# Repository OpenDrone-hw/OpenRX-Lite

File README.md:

# OpenRX Lite

Open-source 2.4 GHz ExpressLRS radio control receiver module with telemetry,
for any radio-controlled build: cars, boats, robots and aircraft. OpenRX Lite
combines an ESP32-C3 and SX1281 with an on-board ceramic link antenna in a
10.0 x 11.5 mm board.
It passes the received channels over serial (CRSF) on its RX and TX pads to a
controller, for example a flight controller or a vehicle or robot controller.

## Specifications

| | |
|---|---|
| Band | 2.4 GHz |
| Radio | SX1281 |
| Antenna | On-board ceramic |
| Telemetry power | 13 dBm (20 mW) |
| Protocol | CRSF |
| MCU | ESP32-C3 |
| Input | 5 V pad |
| Firmware | ExpressLRS |
| Flashing | Betaflight passthrough or Wi-Fi |
| Dimensions | 10.0 x 11.5 mm |
| PCB | 6-layer, 1.0 mm |

Technical write-up, part list and layout constraints: [AGENTS.md](AGENTS.md).

## In the line

What pairs with what, and what is available:
[opendrone.be](https://opendrone.be).

## Contributing

To load the KiCad-Library, use `git submodule update --init` or `git clone --recurse-submodules https://github.com/OpenDrone-hw/OpenRX-Lite`

Furthermore, see [CONTRIBUTING.md](CONTRIBUTING.md).

## License

Hardware licensed under [CERN-OHL-S-2.0](https://ohwr.org/cern_ohl_s_v2.txt),
see [LICENSE](LICENSE).

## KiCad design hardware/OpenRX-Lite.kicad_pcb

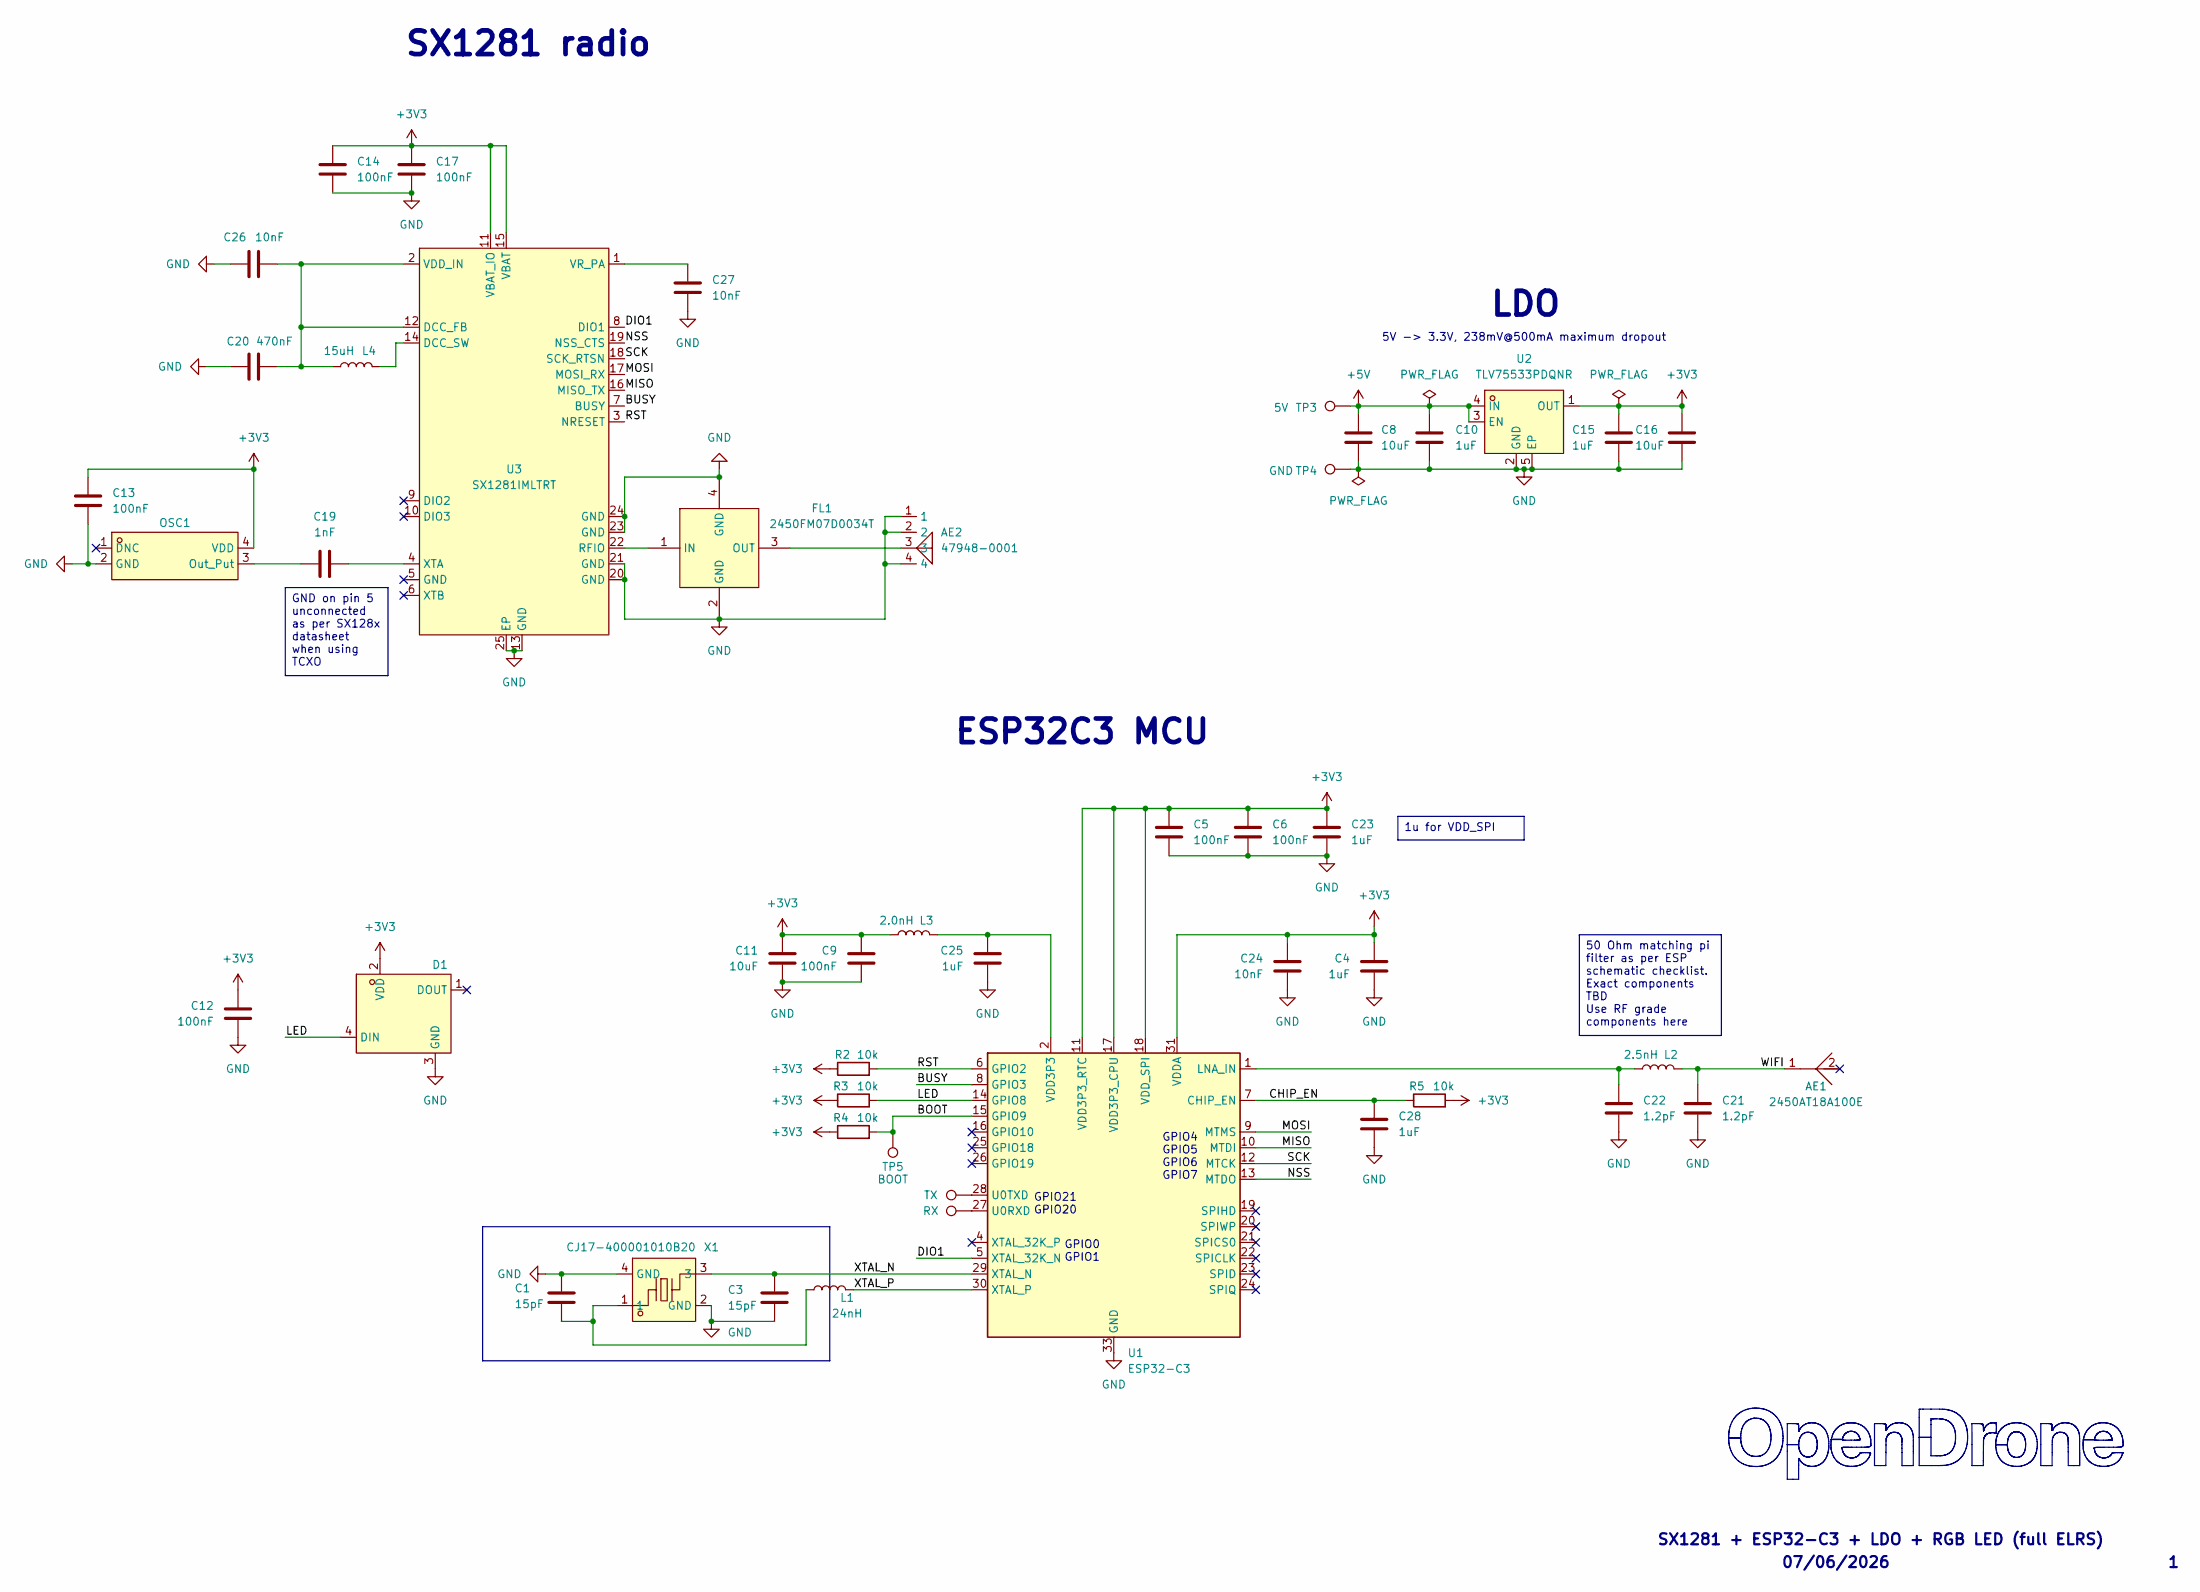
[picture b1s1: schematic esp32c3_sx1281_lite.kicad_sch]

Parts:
AE1: 2450AT18A100E; ANT-SMD_L3.2-W1.6; MPN 2450AT18A100E; LCSC Part C89334
AE2: 47948-0001; ANT-SMD_47948-0001; MPN 479480001; LCSC C152351
C1, C3: 15pF; C_0201_0603Metric; MPN GRM0335C1H150JA01D; LCSC C85891
C4, C10, C15, C23, C25, C28: 1uF; C_0201_0603Metric; MPN GRM033R61A105ME44D; LCSC C76935
C5, C6, C9, C12, C13, C14, C17: 100nF; C_0201_0603Metric; MPN GRM033R61E104KE14D; LCSC C76939
C8, C16: 10uF; C_0402_1005Metric; MPN CL05A106MQ5NUNC; LCSC C15525
C11: 10uF; C_0402_1005Metric; MPN GRM155R60J106ME44D; LCSC C76991
C19: 1nF; C_0201_0603Metric; MPN 0201B102K500NT; LCSC C66942
C20: 470nF; C_0201_0603Metric; MPN GRM033R60J474KE90D; LCSC C85926
C21, C22: 1.2pF; C_0201_0603Metric; MPN GRM0335C1H1R2BA01D; LCSC C85895
C24, C26, C27: 10nF; C_0201_0603Metric; MPN GRM033R61A103KA01J; LCSC C2168164
D1: XL-1010RGBC-WS2812B; LED-SMD_4P-L1.0-W1.0-TL_XL-1010RGBC-WS2812B; MPN XL-1010RGBC-2812B; LCSC C5349953
FL1: 2450FM07D0034T; FILTER-SMD_4P-L1.0-W0.5-L; MPN 2450FM07D0034T; LCSC Part_1 C2651081
L1: 24nH; L_0201_0603Metric; MPN LQP03TN24NH02D; LCSC C206441
L2: 2.5nH; L_0201_0603Metric; MPN LQP03TN2N5C02D; LCSC C206435
L3: 2.0nH; L_0201_0603Metric; MPN LQP03TN2N0B02D; LCSC C86125
L4: 15uH; L_0805_2012Metric; MPN MLZ2012M150WT000; LCSC C383402
OSC1: OW7EL89CENUNFAYLC-52M; OSC-SMD_4P-L2.0-W1.6-BL_TXC_7Z; MPN OW7EL89CENUNFAYLC-52M; LCSC Part C22434896
R2, R3, R4, R5: 10k; R_0201_0603Metric; MPN RC0201FR-0710KL; LCSC C106225
TP1: RX; SolderPad_1.2x2.0mm
TP2: TX; SolderPad_1.2x2.0mm
TP3: 5V; SolderPad_1.2x2.0mm
TP4: GND; SolderPad_1.2x2.0mm
TP5: BOOT; SolderPad_1.2x2.0mm
U1: ESP32-C3; QFN-32-1EP_5x5mm_P0.5mm_EP3.7x3.7mm; MPN ESP32-C3FH4; LCSC C2858491
U2: TLV75533PDQNR; X2SON-4_L1.0-W1.0-P0.65-TL-EP; MPN TLV75533PDQNR; LCSC Part C2861882
U3: SX1281IMLTRT; QFN-24_L4.0-W4.0-P0.50-TL-EP2.6; MPN SX1281IMLTRT; LCSC Part C2151551
X1: CJ17-400001010B20; CRYSTAL-SMD_4P-L1.6-W1.2-BL; MPN CJ17-400001010B20; LCSC Part C2875272

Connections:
+3V3: C4.1, C5.1, C6.1, C9.1, C11.1, C12.1, C13.1, C14.1, C15.1, C16.1, C17.1, C23.1, C24.1, D1.2 (VDD), L3.2, OSC1.4 (VDD), R2.1, R3.1, R4.1, R5.2, U1.11 (VDD3P3_RTC), U1.17 (VDD3P3_CPU), U1.18 (VDD_SPI), U1.31 (VDDA), U1.32 (VDDA), U2.1 (OUT), U3.11 (VBAT_IO), U3.15 (VBAT)
+5V: C8.1, C10.1, TP3.1 (1_1), U2.3 (EN), U2.4 (IN)
/ESP32-C3 + SX1281 Core (UFL)/BOOT: R4.2, TP5.1 (1_1), U1.15 (GPIO9)
/ESP32-C3 + SX1281 Core (UFL)/BUSY: U1.8 (GPIO3), U3.7 (BUSY)
/ESP32-C3 + SX1281 Core (UFL)/CHIP_EN: C28.1, R5.1, U1.7 (CHIP_EN)
/ESP32-C3 + SX1281 Core (UFL)/DIO1: U1.5 (XTAL_32K_N), U3.8 (DIO1)
/ESP32-C3 + SX1281 Core (UFL)/LED: D1.4 (DIN), R3.2, U1.14 (GPIO8)
/ESP32-C3 + SX1281 Core (UFL)/MISO: U1.10 (MTDI), U3.16 (MISO_TX)
/ESP32-C3 + SX1281 Core (UFL)/MOSI: U1.9 (MTMS), U3.17 (MOSI_RX)
/ESP32-C3 + SX1281 Core (UFL)/NSS: U1.13 (MTDO), U3.19 (NSS_CTS)
/ESP32-C3 + SX1281 Core (UFL)/RST: R2.2, U1.6 (GPIO2), U3.3 (NRESET)
/ESP32-C3 + SX1281 Core (UFL)/SCK: U1.12 (MTCK), U3.18 (SCK_RTSN)
/ESP32-C3 + SX1281 Core (UFL)/WIFI: AE1.1, C21.1, L2.1
/ESP32-C3 + SX1281 Core (UFL)/XTAL_N: C3.1, U1.29 (XTAL_N), X1.3
/ESP32-C3 + SX1281 Core (UFL)/XTAL_P: L1.2, U1.30 (XTAL_P)
GND: AE2.1, AE2.2, AE2.4, C1.2, C3.2, C4.2, C5.2, C6.2, C8.2, C9.2, C10.2, C11.2, C12.2, C13.2, C14.2, C15.2, C16.2, C17.2, C20.1, C21.2, C22.2, C23.2, C24.2, C25.2, C26.1, C27.2, C28.2, D1.3 (GND), FL1.2 (GND), FL1.4 (GND), OSC1.2 (GND), TP4.1 (1_1), U1.33 (GND), U2.2 (GND), U2.5 (EP), U3.13 (GND), U3.20 (GND), U3.21 (GND), U3.23 (GND), U3.24 (GND), U3.25 (EP), X1.2 (GND), X1.4 (GND)
unnamed: C1.1, L1.1, X1.1
unnamed: C25.1, L3.1, U1.2 (VDD3P3), U1.3 (VDD3P3)
unnamed: FL1.1 (IN), U3.22 (RFIO)
unnamed: AE2.3, FL1.3 (OUT)
unnamed: C19.1, OSC1.3 (Out_Put)
unnamed: C22.1, L2.2, U1.1 (LNA_IN)
unnamed: TP1.1 (1_1), U1.27 (U0RXD)
unnamed: TP2.1 (1_1), U1.28 (U0TXD)
unnamed: C20.2, C26.2, L4.1, U3.2 (VDD_IN), U3.12 (DCC_FB)
unnamed: L4.2, U3.14 (DCC_SW)
unnamed: C27.1, U3.1 (VR_PA)
unnamed: C19.2, U3.4 (XTA)

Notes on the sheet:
5V -> 3.3V, 238mV@500mA maximum dropout
GPIO0 GPIO1
SX1281 + ESP32-C3 + LDO + RGB LED (full ELRS)
GPIO21 GPIO20
GPIO4 GPIO5 GPIO6 GPIO7
SX1281 radio
LDO
ESP32C3 MCU
07/06/2026
GND on pin 5 unconnected as per SX128x datasheet when using TCXO
1u for VDD_SPI
50 Ohm matching pi filter as per ESP schematic checklist. Exact components TBD Use RF grade components here

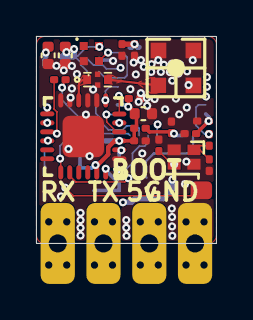
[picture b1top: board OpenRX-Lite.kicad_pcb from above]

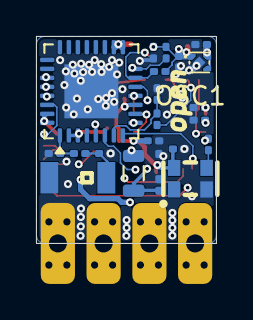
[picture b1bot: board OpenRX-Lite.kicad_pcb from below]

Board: 6 copper layers, 10.0 x 11.5 mm, 47 parts (22 on the bottom side), 28 nets.

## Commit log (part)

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2026-03-23 Initial repo: 6-receiver product lineup, core BOM, shared datasheets
    OpenRX is an open-source ExpressLRS 4.0 receiver family covering
    budget nano to Xrossband Gemini. All designs use ESP32-C3 MCU with
    SX1281 (2.4GHz) or LR1121 (dual-band) RF transceivers.
    CERN-OHL-S v2 licensed. Part of the OpenDrone ecosystem.
2026-03-23 Add OpenRX-Lite: budget 2.4GHz receiver (ESP32-C3 + SX1281)
    Smallest/cheapest receiver. No PA/LNA, ceramic antenna, 16x12mm.
    Includes SCHEMATIC.md, BOM.md, imported LCSC libs, datasheets.
    KiCad schematic/PCB are starter shells awaiting capture.
2026-03-23 Consolidate docs: 1 README + KICAD_WORKFLOW + 1 DESIGN.md per receiver
    - Merge SCHEMATIC.md + BOM.md into single DESIGN.md per receiver
    - Delete OPENRX_ELRS_4_RECEIVER_PORTFOLIO.md (content integrated)
    - Delete REPO_AUDIT_2026-03-23.md (issues addressed)
    - Fold CORE_BOM into README.md architecture table
    - Rename KICAD_WORKFLOW_AND_ELRS_COMPATIBILITY.md to KICAD_WORKFLOW.md
    - Rewrite KICAD_WORKFLOW with step-by-step capture instructions
2026-03-23 Fix all DESIGN.md: RFX2401C, DEA LPF, LR1121 pinout, FEM control
    - Lite: remove L-match network, use DEA102700LT-6307A2 only
    - Nano: clarify DEA LPF path, mark 0.3pF as mandatory, SE2431L as EOL
    - 900: fix LR1121 RFSW description, confirm 4x4mm package
    - Dual: SE2431L→RFX2401C, FEM via LR1121 RFSW not MCU GPIO, BOM $9→$7.62
    - PWM: SE2431L→RFX2401C, DEA LPF + 0.3pF path, BOM $7.40→$6.02
    - Gemini: SE2431L→RFX2401C, fix FEM control model, BOM $10.84→$9.46
2026-03-23 Update all DESIGN.md: TLV75533 X2SON LDO, XL-1010 1x1mm LED
    - Lite/Nano/900/Dual: ME6211 SOT-23-5 → TLV75533PDQNR X2SON-4 (1x1mm)
    - Gemini: keeps AP2112K (600mA needed for dual radios)
    - PWM: keeps AMS1117 (needs >6V input range)
    - All: WS2812B-2020 → XL-1010RGBC-WS2812B (1x1mm)
    - Updated cap values for TLV755 (1uF local + 10uF bulk)
2026-03-23 Import DEA102700LT-6307A2 LPF into shared library (C574024)
2026-03-23 Import U.FL-R-SMT-1(80) UFL connector into shared library (C88374)
2026-03-23 Import Molex 479480001 tower ceramic antenna (C152351) for ELRS RF
2026-03-23 Add solder pad footprints: 1.0x1.5mm and 1.0x0.8mm compact
2026-03-23 Unify library tables, import RFX2401C, Lite schematic capture
    - All 6 projects now share OpenRX-Shared + OpenRX-Lite lib tables
    - Import RFX2401C (C19213) into shared library with 3D model path fix
    - OpenRX-Lite schematic: 0 ERC errors (captured in KiCad GUI)
    - Add .gitignore for .lck and .history files
2026-03-23 Separate Lite and Nano schematics, stop sharing one file
    Sharing one .kicad_sch between projects doesn't work - KiCad
    overwrites instance data when either project saves.
    - Lite: restored pre-Nano schematic as local esp32c3_sx1281_lite.kicad_sch
    - Nano: copied current shared sheet as local esp32c3_sx1281_rx_core.kicad_sch
    - Each project now has its own schematic file
2026-03-23 Lite + Nano schematics: LCSC fields, fix 10uF to 0402, drop 0.3pF cap
    - All passives in both schematics have LCSC fields
    - 10uF caps fixed from 0201 to 0402 (C15525)
    - Nano C22 (0.3pF): removed discrete cap, use trace capacitance instead
    - 0 ERC errors on both schematics
2026-03-23 Import LR1121 (C7498014) and 32MHz TCXO (C22434888) into shared library
2026-03-23 Import Johanson 0900PC16J0042001E LR11xx sub-GHz IPD (C19842466) and LR1121 + 32MHz TCXO
2026-03-23 OpenRX-900: add all LCSC fields, fix 4.7uF to 0402
    - C20 (4.7uF): C23733, footprint fixed from 0201 to 0402
    - R5/R6/R7 (100k): C25741, RFSW pull-downs
    - L1 (10uH): C1035, 0603 DC-DC inductor
    - U4 (LR1121): C7498014
    - U5 (32MHz TCXO): C22434888
    - T1 (Johanson IPD): C19842466
2026-03-23 Fix crystal load caps: 10pF → 18pF (C71153) on all 4 receivers
    CJ17-400001010B20 crystal has CL=10pF. With 10pF load caps and
    ~2pF stray, effective load was only 7pF (30% low). Changed to 18pF
    giving ~11pF effective load, matching the crystal spec.
    C71153 = Samsung CL03C180JA3NNNC, 18pF C0G 25V 0201.
2026-03-23 Fix Gemini crystal load caps to 18pF (C62164), matching Lite and Mono
2026-03-23 Repo cleanup: remove ERC reports, lock files, backup dirs, fix gitignore
2026-03-23 OpenRX-Gemini: dual LR1121 schematic complete, 0 ERC errors
    - Radio 1 (U4): sub-GHz via Johanson IPD → JP1 UFL
    - Radio 2 (U9): 2.4GHz via RFX2401C (U10) → DEA (USB2) → JP3 UFL
    - Shared SPI bus (SCK/MISO/MOSI), separate NSS/IRQ/BUSY/RST per radio
    - Radio 2 control: GPIO10=NSS2, GPIO9=IRQ2, GPIO1=BUSY2, GPIO0=RST2
    - FEM driven by Radio 2 RFSW (DIO5→RXEN, DIO6→TXEN)
    - Radio 1 DIO5/DIO6 have 100k pull-downs (disconnected from FEM)
2026-03-23 Add SolderPad_1.2x2.0mm with 25% rounded corners, 2.0mm pitch standard
2026-03-23 Swap all solder pads to 1.2x2.0mm rounded (25%) across Lite, Mono, Gemini
2026-03-23 Swap 32MHz TCXO to smaller 2016 package (C22381772)
    OW2EL89 (3225, 3.2x2.5mm) → OW7EL89 (2016, 2.0x1.6mm)
    Same YXC family, same pinout, same specs. Saves 1.2x0.9mm per TCXO.
    Affects Mono (1x) and Gemini (2x).
2026-03-23 Import SKY13588-460LF SP3T RF switch (C2151906) into shared library
2026-03-23 Final topology: Mono + Gemini netlist with SKY13588 RF switch
    - SKY13588-460LF imported into shared library
    - Complete netlist for Mono (1×LR1121 + SKY13588 + Johanson IPD + DEA LPF → 1 UFL)
    - Gemini = 2× Mono RF chains + ESP32-C3 True Diversity GPIO mapping
    - GPIO maps match official ELRS Generic C3 LR1121 and True Diversity targets
    - Routing notes for RF paths included
    - Mono needs complete GPIO rewire to match ELRS target
2026-03-23 FINAL_NETLIST v3: SKY13588 as band combiner, RFX2401C kept for 100mW
    Based on RadioMaster XR4 teardown analysis:
    - SKY13588 serves as both sub-GHz path switch AND band combiner
    - Johanson IPD in direct-tie mode (RX/TX_LP/TX_HP joined) → SKY13588 J1
    - 2.4GHz: RFIO_HF → DEA LPF → RFX2401C → SKY13588 J2
    - SKY13588 RFC → DC block → UFL → dual-band antenna
    - RFX2401C kept for 100mW market parity
2026-03-24 Repo cleanup: final state for handoff
    - Clean README with architecture, BOM, CE notes, status
    - Remove dated analysis files (absorbed into FINAL_NETLIST + KICAD_WORKFLOW)
    - Remove stale OpenRX-Dual (archived), ERC reports, backups, prl files
    - Updated .gitignore for .kicad_dru, production backups
    - CERN-OHL-S v2 license confirmed
    - 3 active projects: Lite, Mono, Gemini
2026-03-24 Revise target prices in receiver specifications
    Updated target prices for Lite, Mono, and Gemini models.
2026-03-24 Consolidate active RX docs and shared project metadata
2026-04-21 initial routing for all
2026-04-27 final route
2026-04-28 Set via netclass + dimension defaults to 0.3/0.2mm on all 4 boards
2026-04-28 switch to 0.2mm vias
2026-04-28 gitignore JLC per-quote BOM markdown drops
2026-05-08 OpenRX Lite (UFL + molex)
2026-05-13 fab and placement output for combined order
2026-06-07 annotate
